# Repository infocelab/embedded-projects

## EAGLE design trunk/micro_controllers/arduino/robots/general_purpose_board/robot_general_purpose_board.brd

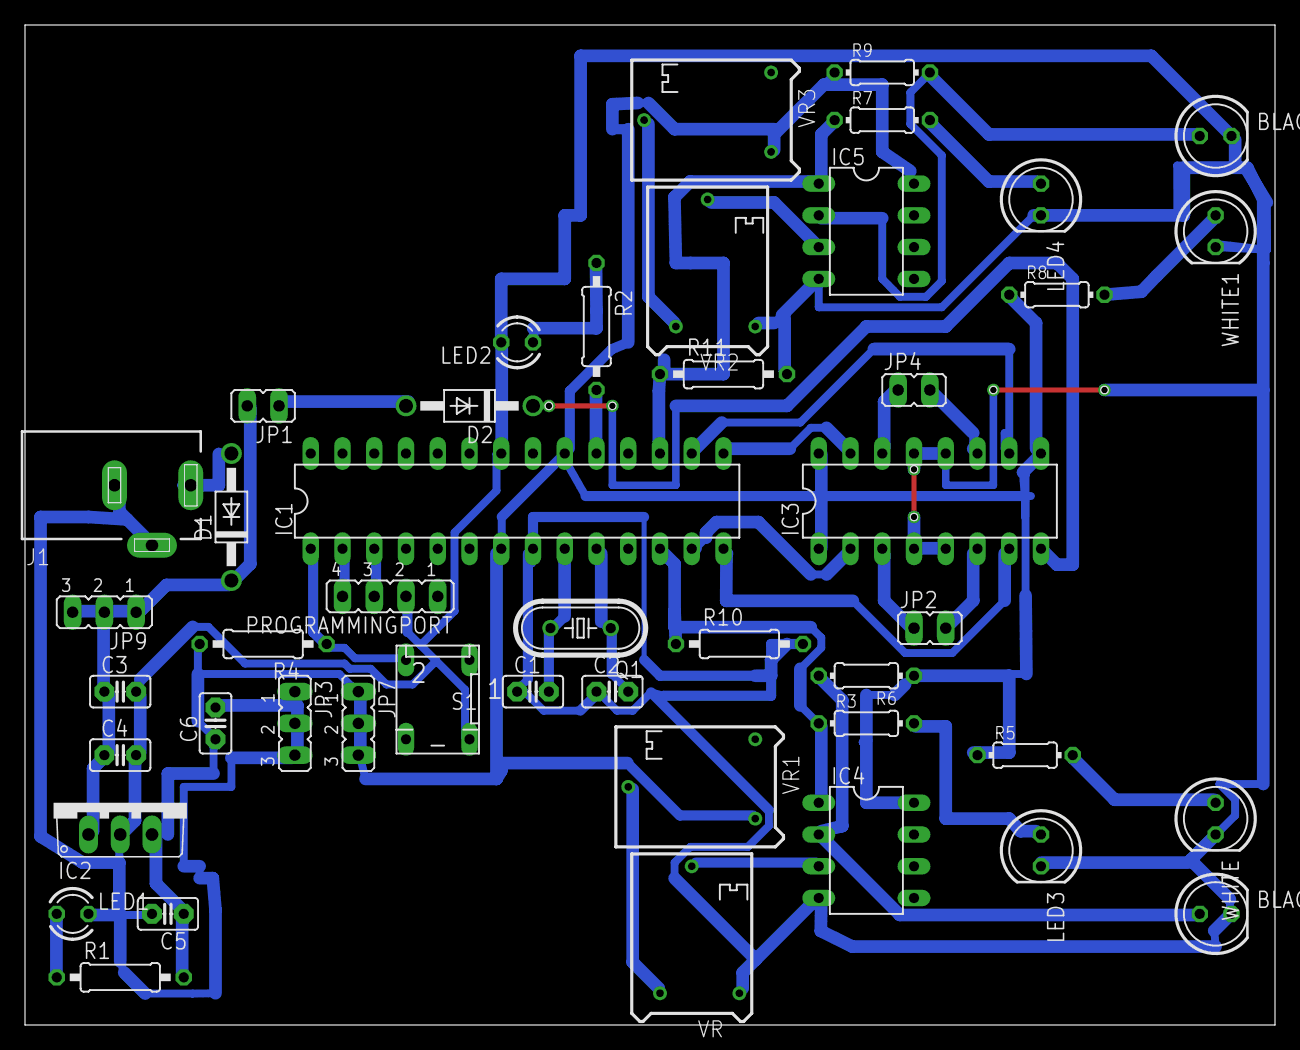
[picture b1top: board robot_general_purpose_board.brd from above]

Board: 2 copper layers, 100.0 x 80.0 mm, 46 parts (0 on the bottom side), 34 nets.

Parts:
BLACK, BLACK1: 5mm; LED5MM
C1, C2: 22pf; C2.5-2
C3: 470Uf; C2.5-2
C4, C5: 0.1uf; C2.5-2
C6: 4.7uf; C2.5-2
D1, D2: 1N4007; DO41-10
IC1: ATMEGA328; DIL28-3
IC2: 7805; TO220V
IC3: L293D; DIL16
IC4, IC5: 358; DIL-08
J1: DCJ0303
JP1, JP2, JP4: JP1
JP3: 0volt; JP2
JP7: +5v0lt; JP2
JP9: +12volt; JP2
LED1, LED2: LED3MM
LED3, LED4: 5mm; LED5MM
PROGRAMMINGPORT: JP4
Q1: 16MHZ; HC49/S
R1: 220R; 0207/10
R2: 330R; 0207/10
R3, R5, R7, R8: 1K; 0204/7
R4, R10, R11: 10K; 0207/10
R6, R9: 10K; 0204/7
S1: DP-02
VR, VR2: 50k; RTRIM64P
VR1, VR3: 100E; RTRIM64P
WHITE, WHITE1: 5mm; LED5MM

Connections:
+5V: C5.1, C6.1, IC1.7, IC1.20, IC2.3, IC3.1, IC3.9, IC3.16, IC4.8, IC5.8, JP7.1, JP7.2, JP7.3, R1.2, R4.2, R5.1, R6.1, R8.1, R9.1, VR1.3, VR3.3
+12V: C3.1, C4.1, D1.C, IC2.1, JP1.2, JP9.1, JP9.2, JP9.3
GND: BLACK.K, BLACK1.K, C1.1, C2.1, C3.2, C4.2, C5.2, C6.2, IC1.8, IC1.22, IC2.2, IC3.4, IC3.5, IC3.12, IC3.13, IC4.4, IC5.4, J1.2, J1.3, JP3.1, JP3.2, JP3.3, LED1.K, LED2.K, LED3.K, LED4.K, PROGRAMMINGPORT.2, R10.2, R11.2, S1.4, VR.1, VR2.1, WHITE.K, WHITE1.K
unnamed: C1.2, IC1.9, Q1.2
unnamed: C2.2, IC1.10, Q1.1
unnamed: D1.A, J1.1
unnamed: LED2.A, R2.1
unnamed: LED1.A, R1.1
unnamed: D2.C, IC3.8
unnamed: D2.A, JP1.1
unnamed: IC3.14, JP4.1
unnamed: IC3.11, JP4.2
unnamed: IC3.3, JP2.1
unnamed: IC3.6, JP2.2
unnamed: IC1.2, PROGRAMMINGPORT.4
unnamed: IC1.12, IC4.1, R3.1, R10.1
unnamed: R5.2, WHITE.A
unnamed: BLACK.A, IC4.2, R6.2
unnamed: IC1.15, IC3.15
unnamed: IC1.16, IC3.10
unnamed: IC1.14, IC3.7
unnamed: IC1.17, IC5.1, R7.1, R11.1
unnamed: IC1.19, R2.2
unnamed: IC4.3, VR.2
unnamed: VR.3, VR1.2
unnamed: IC1.3, PROGRAMMINGPORT.3
unnamed: IC1.1, R4.1, S1.2
unnamed: LED3.A, R3.2
unnamed: IC1.13, IC3.2
unnamed: R8.2, WHITE1.A
unnamed: BLACK1.A, IC5.2, R9.2
unnamed: IC5.3, VR2.2
unnamed: VR2.3, VR3.2
unnamed: LED4.A, R7.2

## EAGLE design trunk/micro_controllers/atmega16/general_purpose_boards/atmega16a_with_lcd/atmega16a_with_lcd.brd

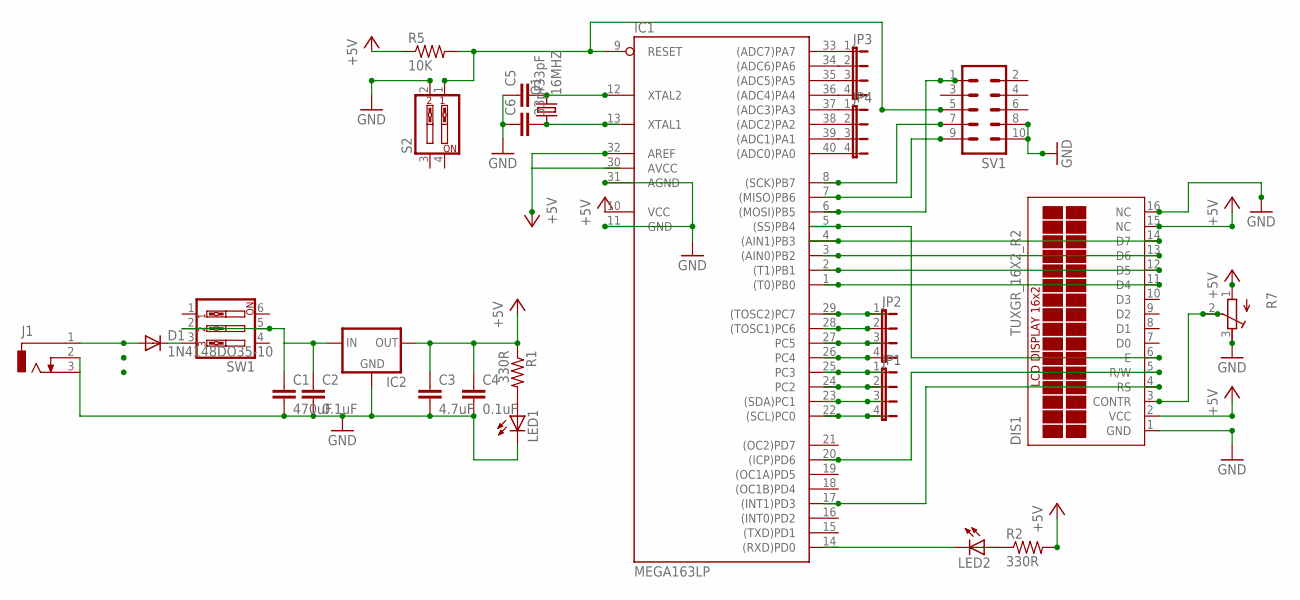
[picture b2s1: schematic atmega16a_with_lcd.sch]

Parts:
C1: 470uF; C2.5-4
C2, C4: 0.1uF; C2.5-4
C3: 4.7uF; C2.5-4
C5, C6: 33pF; C2.5-4
D1: 1N4148DO35-10; DO35-10
DIS1: TUXGR_16X2_R2
IC1: MEGA163LP; DIL40
IC2: 78XXS
J1: DCJ0303
JP1, JP2, JP3, JP4: JP4E; JP4
LED1, LED2: LED_ELD260; LED_LD260
Q1: 16MHZ; HC49U-V
R1, R2: 330R; 0204/7
R5: 10K; 0204/7
R7: R-TRIMM3339P; RTRIM3339P
S2: SW_DIP-2; EDG-02
SV1: MA05-2
SW1: SW_DIP-3; EDG-03

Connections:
+5V: C3.1, C4.1, DIS1.2 (VCC), DIS1.15 (NC), IC1.10 (VCC), IC1.32 (AREF), IC2.OUT, R1.1, R2.2, R5.1, R7.1 (E)
AVCC: IC1.30 (AVCC)
GND: C1.2, C2.2, C3.2, C4.2, C5.1, C6.1, DIS1.1 (GND), DIS1.16 (NC), IC1.11 (GND), IC1.31 (AGND), IC2.GND, J1.2, J1.3, LED1.K (C), R7.3 (A), S2.2, SV1.8, SV1.10
unnamed: D1.A, J1.1
unnamed: IC1.29 ((TOSC2)PC7), JP2.1
unnamed: C5.2, IC1.12 (XTAL2), Q1.2
unnamed: C6.2, IC1.13 (XTAL1), Q1.1
unnamed: LED1.A, R1.2
unnamed: IC1.9 (RESET), R5.2, S2.1, SV1.5
unnamed: DIS1.3 (CONTR), R7.2 (S)
unnamed: D1.C, SW1.3
unnamed: C1.1, C2.1, IC2.IN, SW1.2, SW1.5
unnamed: DIS1.11 (D4), IC1.1 ((T0)PB0)
unnamed: DIS1.12 (D5), IC1.2 ((T1)PB1)
unnamed: DIS1.13 (D6), IC1.3 ((AIN0)PB2)
unnamed: DIS1.14 (D7), IC1.4 ((AIN1)PB3)
unnamed: DIS1.4 (RS), IC1.17 ((INT1)PD3)
unnamed: DIS1.5 (R/W), IC1.20 ((ICP)PD6)
unnamed: DIS1.6 (E), IC1.5 ((SS)PB4)
unnamed: IC1.28 ((TOSC1)PC6), JP2.2
unnamed: IC1.27 (PC5), JP2.3
unnamed: IC1.26 (PC4), JP2.4
unnamed: IC1.25 (PC3), JP1.1
unnamed: IC1.24 (PC2), JP1.2
unnamed: IC1.23 ((SDA)PC1), JP1.3
unnamed: IC1.22 ((SCL)PC0), JP1.4
unnamed: IC1.6 ((MOSI)PB5), SV1.1
unnamed: IC1.7 ((MISO)PB6), SV1.9
unnamed: IC1.8 ((SCK)PB7), SV1.7
unnamed: IC1.14 ((RXD)PD0), LED2.K (C)
unnamed: IC1.33 ((ADC7)PA7), JP3.1
unnamed: IC1.34 ((ADC6)PA6), JP3.2
unnamed: IC1.35 ((ADC5)PA5), JP3.3
unnamed: IC1.36 ((ADC4)PA4), JP3.4
unnamed: IC1.37 ((ADC3)PA3), JP4.1
unnamed: IC1.38 ((ADC2)PA2), JP4.2
unnamed: IC1.39 ((ADC1)PA1), JP4.3
unnamed: IC1.40 ((ADC0)PA0), JP4.4
unnamed: LED2.A, R2.1

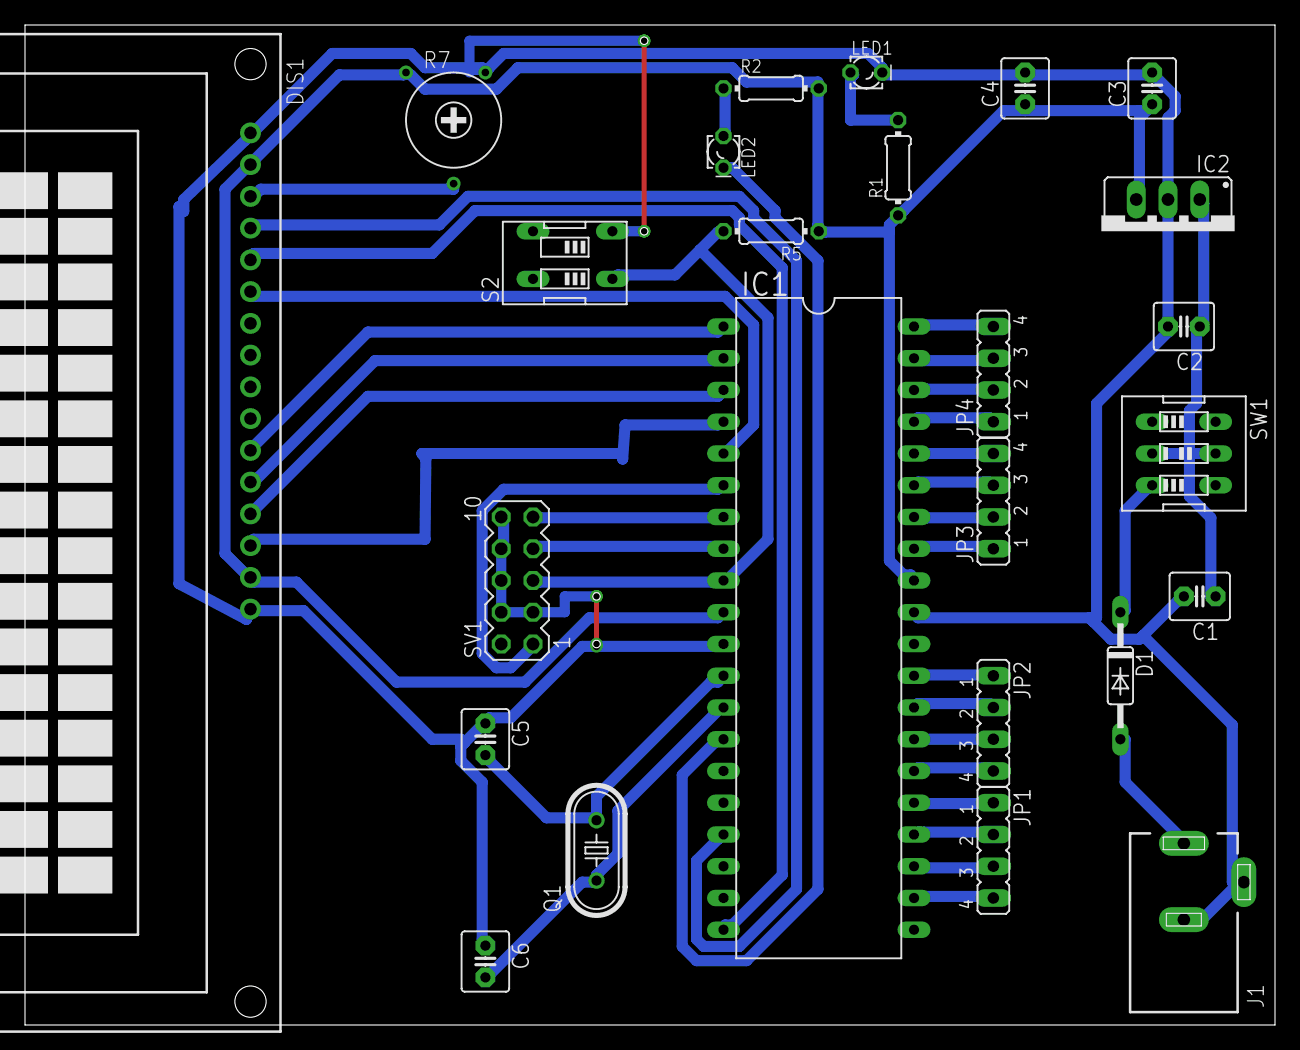
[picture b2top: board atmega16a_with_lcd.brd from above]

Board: 2 copper layers, 100.0 x 80.0 mm, 25 parts (0 on the bottom side), 38 nets.

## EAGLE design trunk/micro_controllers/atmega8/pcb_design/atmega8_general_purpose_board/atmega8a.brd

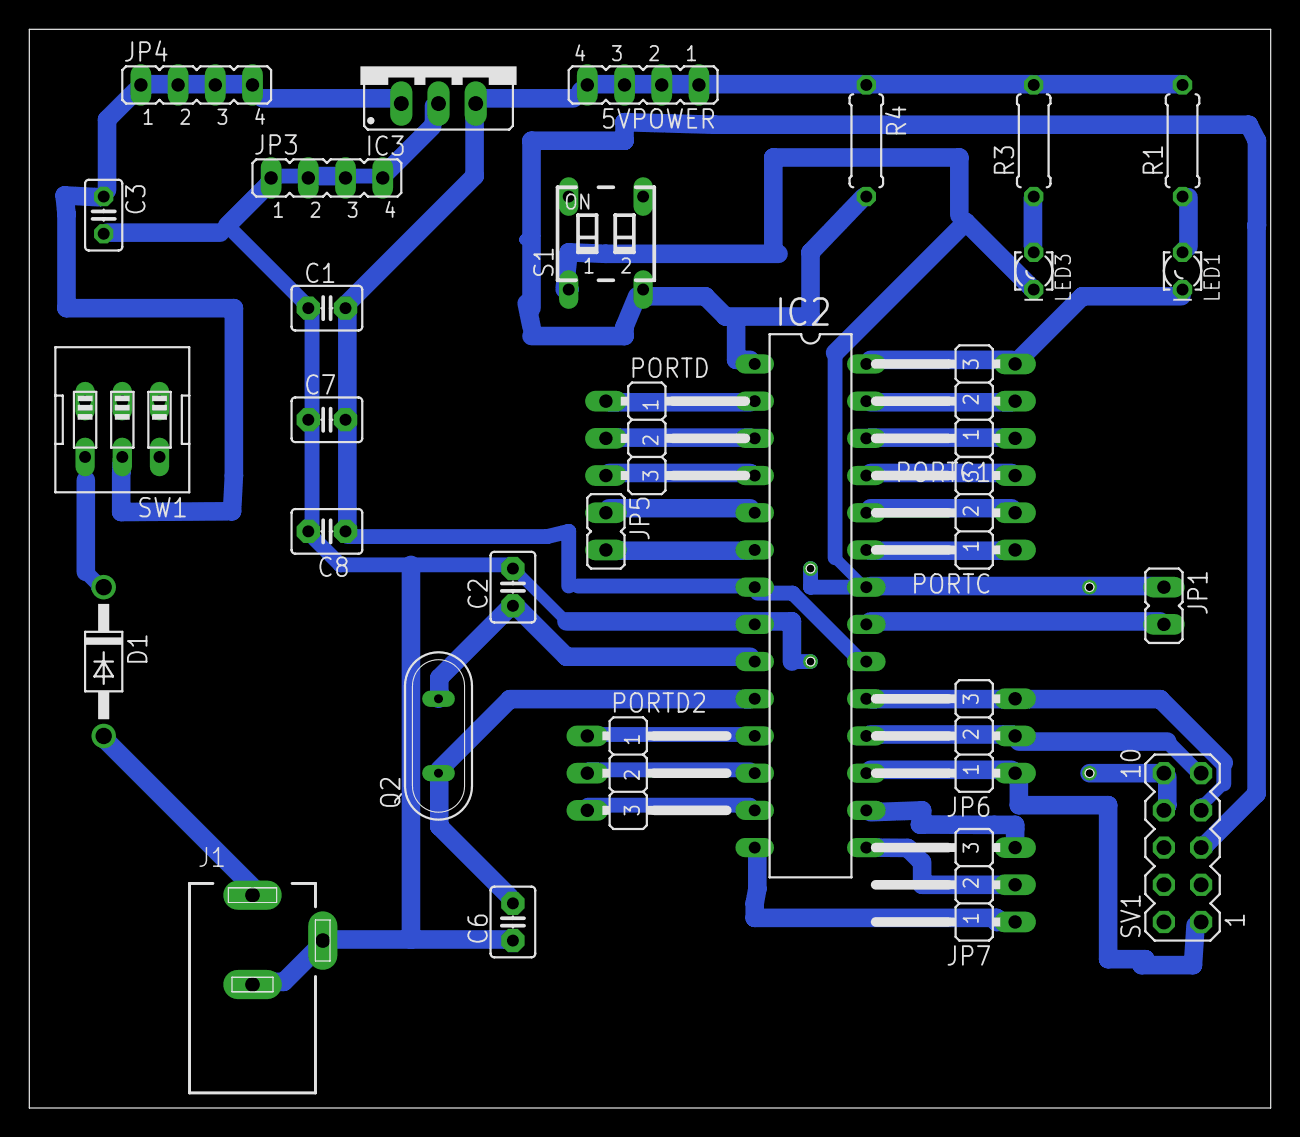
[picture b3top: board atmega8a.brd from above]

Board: 2 copper layers, 84.8 x 73.7 mm, 30 parts (0 on the bottom side), 31 nets.

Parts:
5VPOWER: 5V; JP4
C1, C7, C8: 0.1uf; C2.5-3
C2, C6: 22pf; C2.5-3
C3: 100uf; C025-025X050
D1: 1N4004; DO41-10
IC2: MEGA8-P; DIL28-3
IC3: 78XXS
J1: DCJ0202
JP1, JP5: JP1
JP3: GND; JP4
JP4: 12V; JP4
JP6, JP7: JP2W
LED1, LED3: LED_LD260
PORTC, PORTC1: JP2W
PORTD, PORTD2: JP2W
Q2: QS
R1, R3: 330R; 0207/7
R4: 10K; 0207/7
S1: SD4-02
SV1: MA05-2
SW1: EDG-03

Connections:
unnamed: C3.1, IC3.IN, JP4.1, JP4.2, JP4.3, JP4.4, SW1.5
unnamed: LED1.A, R1.1
unnamed: D1.A, J1.1
unnamed: IC2.23, PORTC.1
unnamed: IC2.24, PORTC.2
unnamed: IC2.25, PORTC.3
unnamed: IC2.26, PORTC1.1
unnamed: D1.C, SW1.4
unnamed: LED3.A, R3.1
unnamed: C2.1, IC2.9, Q2.2
unnamed: C6.2, IC2.10, Q2.1
unnamed: 5VPOWER.1, 5VPOWER.2, 5VPOWER.3, 5VPOWER.4, C1.2, C7.2, C8.1, IC2.7, IC2.20, IC3.OUT, R1.2, R3.2, R4.1
unnamed: IC2.27, PORTC1.2
unnamed: IC2.28, LED1.K, PORTC1.3
unnamed: IC2.2, PORTD.1
unnamed: IC2.3, PORTD.2
unnamed: IC2.4, PORTD.3
unnamed: IC2.5, JP5.1
unnamed: IC2.6, JP5.2
unnamed: IC2.14, JP7.1
unnamed: IC2.15, JP7.2
unnamed: IC2.16, JP7.3
unnamed: IC2.17, JP6.1, SV1.1
unnamed: IC2.18, JP6.2, SV1.9
unnamed: IC2.19, JP6.3, SV1.7
unnamed: C1.1, C2.2, C3.2, C6.1, C7.1, C8.2, IC2.22, IC3.GND, J1.2, J1.3, JP1.1, JP3.1, JP3.2, JP3.3, JP3.4, LED3.K, S1.4, SV1.8, SV1.10
unnamed: IC2.1, R4.2, S1.3, SV1.5
unnamed: IC2.11, PORTD2.1
unnamed: IC2.12, PORTD2.2
unnamed: IC2.13, PORTD2.3
unnamed: IC2.21, JP1.2

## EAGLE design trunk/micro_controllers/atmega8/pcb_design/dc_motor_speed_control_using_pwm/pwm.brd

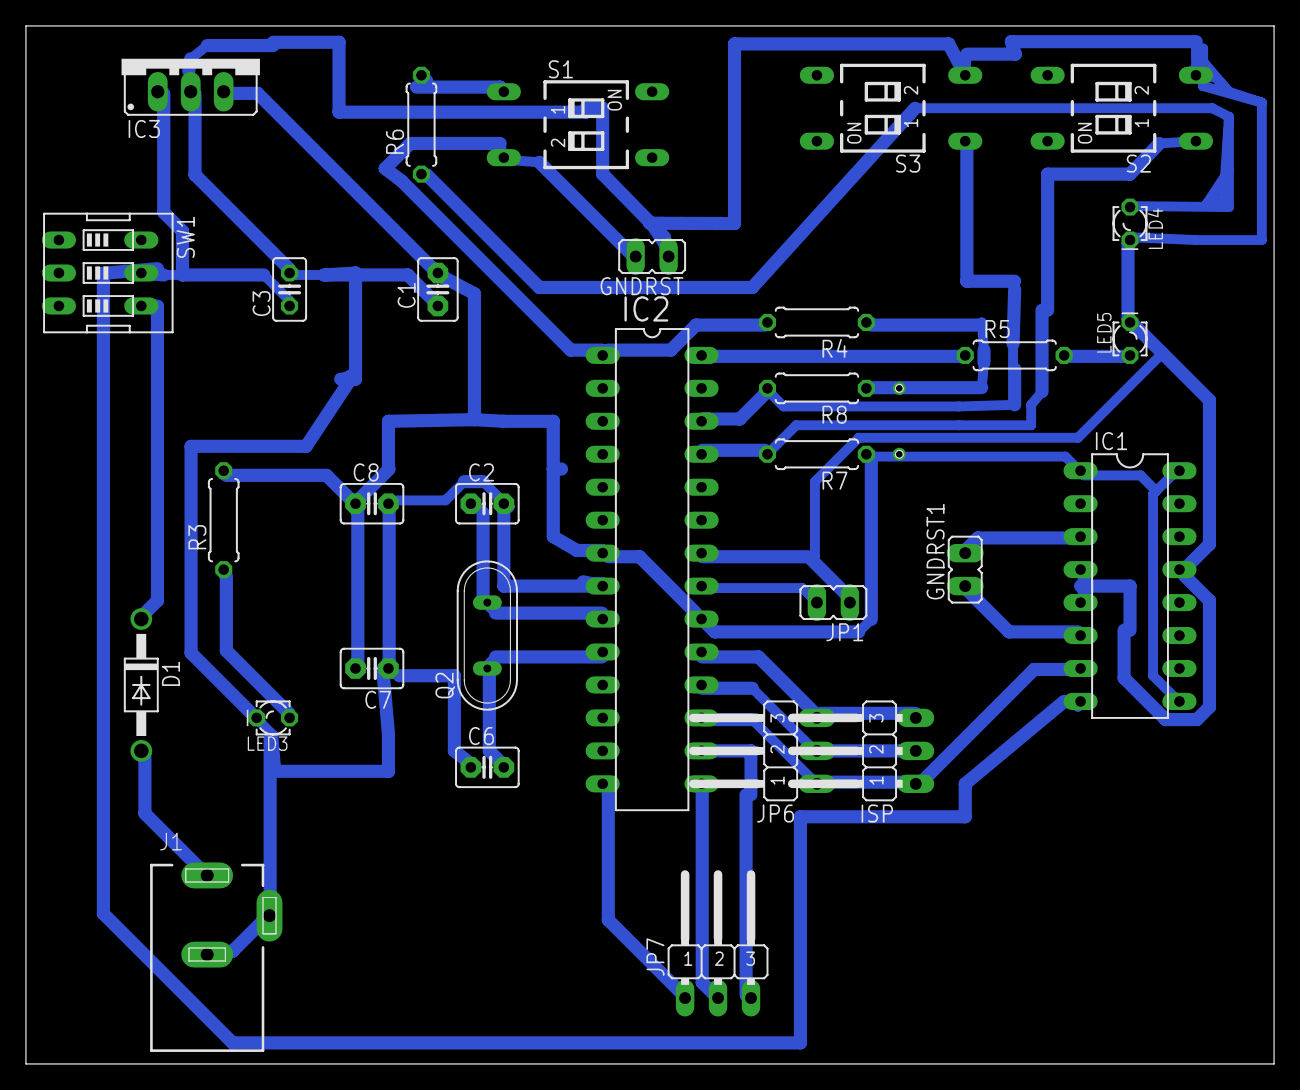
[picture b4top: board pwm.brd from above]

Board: 2 copper layers, 96.2 x 80.0 mm, 31 parts (0 on the bottom side), 24 nets.

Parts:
C1, C7, C8: 0.1uf; C2.5-3
C2, C6: 22pf; C2.5-3
C3: 100uf; C025-025X050
D1: 1N4004; DO41-10
GNDRST, GNDRST1: JP1
IC1: L293D; DIL16
IC2: MEGA8-P; DIL28-3
IC3: 78XXS
ISP: JP2W
J1: DCJ0202
JP1: JP1
JP6, JP7: JP2W
LED3, LED4, LED5: LED_LD260
Q2: QS
R3, R6: 330R; 0207/7
R4, R7, R8: 10K; 0207/7
R5: 0207/7
S1, S2, S3: SD4-02
SW1: EDG-03

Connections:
unnamed: C3.1, IC1.8, IC3.IN, SW1.5
unnamed: D1.A, J1.1
unnamed: GNDRST1.2, IC1.3
unnamed: GNDRST1.1, IC1.6
unnamed: C1.1, C2.2, C3.2, C6.1, C7.1, C8.2, GNDRST.1, IC1.4, IC1.5, IC1.13, IC2.8, IC2.22, IC3.GND, J1.2, J1.3, JP1.1, LED3.K, LED4.K, LED5.K, S2.2, S3.2
unnamed: D1.C, SW1.4
unnamed: LED3.A, R3.1
unnamed: C2.1, IC2.9, Q2.2
unnamed: C6.2, IC2.10, Q2.1
unnamed: C1.2, C7.2, C8.1, IC1.1, IC1.9, IC1.16, IC2.7, IC2.20, IC3.OUT, R3.2, R4.1, R7.1, R8.1
unnamed: LED4.A, R6.1
unnamed: IC2.25, R7.2, S2.1
unnamed: IC2.26, R8.2, S3.1
unnamed: IC2.28, R5.1
unnamed: IC2.14, JP7.1
unnamed: IC2.15, JP7.2
unnamed: IC2.16, JP7.3
unnamed: IC1.7, IC2.17, ISP.1, JP6.1
unnamed: IC2.18, ISP.2, JP6.2
unnamed: IC2.19, ISP.3, JP6.3
unnamed: LED5.A, R5.2
unnamed: R6.2, S1.1
unnamed: GNDRST.2, IC2.1, R4.2, S1.2
unnamed: IC2.21, JP1.2

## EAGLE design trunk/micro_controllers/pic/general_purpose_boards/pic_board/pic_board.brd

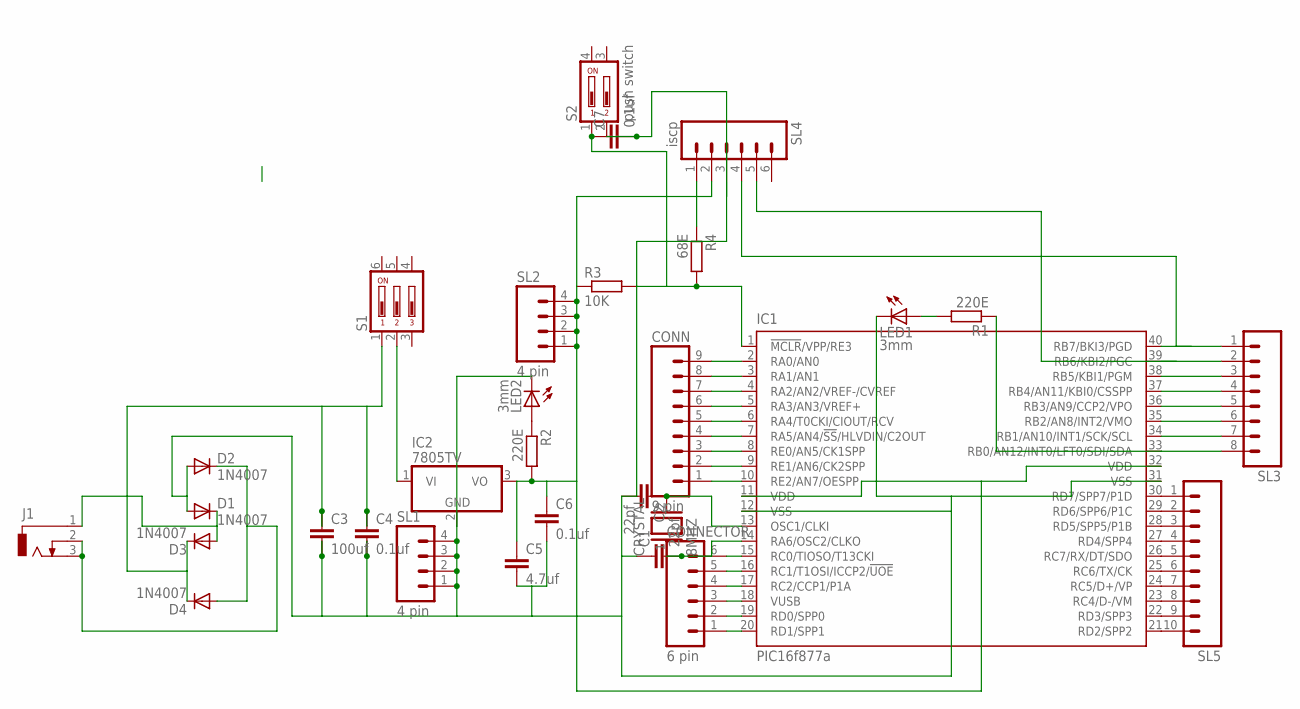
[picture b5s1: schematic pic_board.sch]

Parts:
C1, C2: 22pf; C2.5-2
C3: 100uf; C5B7.2
C4, C7: 0.1uf; C2.5-3
C5: 4.7uf; C5B7.2
C6: 0.1uf; C2.5-2
CONN: 9 pin; 09P
CONNECTOR: 6 pin; 06P
CRYSTAL: 8MHZ; QS
D1, D2, D3, D4: 1N4007; DO41-10
IC1: PIC16f877a; DIL40
IC2: 7805TV; TO220V
J1: DCJ0303
LED1, LED2: 3mm; LED3MM
R1, R2: 220E; 0204/7
R3: 10K; 0204/7
R4: 68E; 0204/7
S1: DA03; DA-03
S2: push switch; DP-02
SL1, SL2: 4 pin; 04P
SL3: M08; 08P
SL4: iscp; 06P
SL5: M10; 10P

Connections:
unnamed: C2.1, CRYSTAL.2, IC1.13 (OSC1/CLKI)
unnamed: C1.2, CRYSTAL.1, IC1.14 (RA6/OSC2/CLKO)
unnamed: LED1.A, R1.2
unnamed: CONN.1, IC1.10 (RE2/AN7/OESPP)
unnamed: CONN.2, IC1.9 (RE1/AN6/CK2SPP)
unnamed: CONN.3, IC1.8 (RE0/AN5/CK1SPP)
unnamed: CONN.4, IC1.7 (RA5/AN4/!SS!/HLVDIN/C2OUT)
unnamed: CONN.5, IC1.6 (RA4/T0CKI/CIOUT/RCV)
unnamed: CONN.6, IC1.5 (RA3/AN3/VREF+)
unnamed: CONN.7, IC1.4 (RA2/AN2/VREF-/CVREF)
unnamed: CONN.8, IC1.3 (RA1/AN1)
unnamed: CONN.9, IC1.2 (RA0/AN0)
unnamed: CONNECTOR.1, IC1.20 (RD1/SPP1)
unnamed: CONNECTOR.2, IC1.19 (RD0/SPP0)
unnamed: CONNECTOR.3, IC1.18 (VUSB)
unnamed: CONNECTOR.4, IC1.17 (RC2/CCP1/P1A)
unnamed: CONNECTOR.5, IC1.16 (RC1/T1OSI/ICCP2/!UOE)
unnamed: CONNECTOR.6, IC1.15 (RC0/TIOSO/T13CKI)
unnamed: IC1.40 (RB7/BKI3/PGD), SL3.1, SL4.4
unnamed: IC1.39 (RB6/KBI2/PGC), SL3.2, SL4.5
unnamed: IC1.38 (RB5/KBI1/PGM), SL3.3
unnamed: IC1.37 (RB4/AN11/KBI0/CSSPP), SL3.4
unnamed: IC1.36 (RB3/AN9/CCP2/VPO), SL3.5
unnamed: IC1.35 (RB2/AN8/INT2/VMO), SL3.6
unnamed: IC1.34 (RB1/AN10/INT1/SCK/SCL), SL3.7
unnamed: IC1.30 (RD7/SPP7/P1D), SL5.1
unnamed: IC1.29 (RD6/SPP6/P1C), SL5.2
unnamed: IC1.28 (RD5/SPP5/P1B), SL5.3
unnamed: IC1.33 (RB0/AN12/INT0/LFT0/SDI/SDA), R1.1, SL3.8
unnamed: C3.1, C4.1, D3.C, D4.C, S1.1
unnamed: D2.C, D4.A, J1.2, J1.3
unnamed: D1.C, D3.A, J1.1
unnamed: C5.1, C6.1, IC1.11 (VDD), IC1.32 (VDD), IC2.3 (VO), R2.2, R3.1, SL2.1, SL2.2, SL2.3, SL2.4, SL4.2
unnamed: LED2.A, R2.1
unnamed: C1.1, C2.2, C3.2, C4.2, C5.2, C6.2, C7.2, D1.A, D2.A, IC1.12 (VSS), IC1.31 (VSS), IC2.2 (GND), LED1.K (C), LED2.K (C), S2.2, SL1.1, SL1.2, SL1.3, SL1.4, SL4.3
unnamed: IC1.27 (RD4/SPP4), SL5.4
unnamed: IC1.26 (RC7/RX/DT/SDO), SL5.5
unnamed: IC1.25 (RC6/TX/CK), SL5.6
unnamed: C7.1, IC1.1 (!MCLR!/VPP/RE3), R3.2, R4.2, S2.1
unnamed: IC1.24 (RC5/D+/VP), SL5.7
unnamed: IC1.23 (RC4/D-/VM), SL5.8
unnamed: IC1.22 (RD3/SPP3), SL5.9
unnamed: IC1.21 (RD2/SPP2), SL5.10
unnamed: R4.1, SL4.1
unnamed: IC2.1 (VI), S1.2

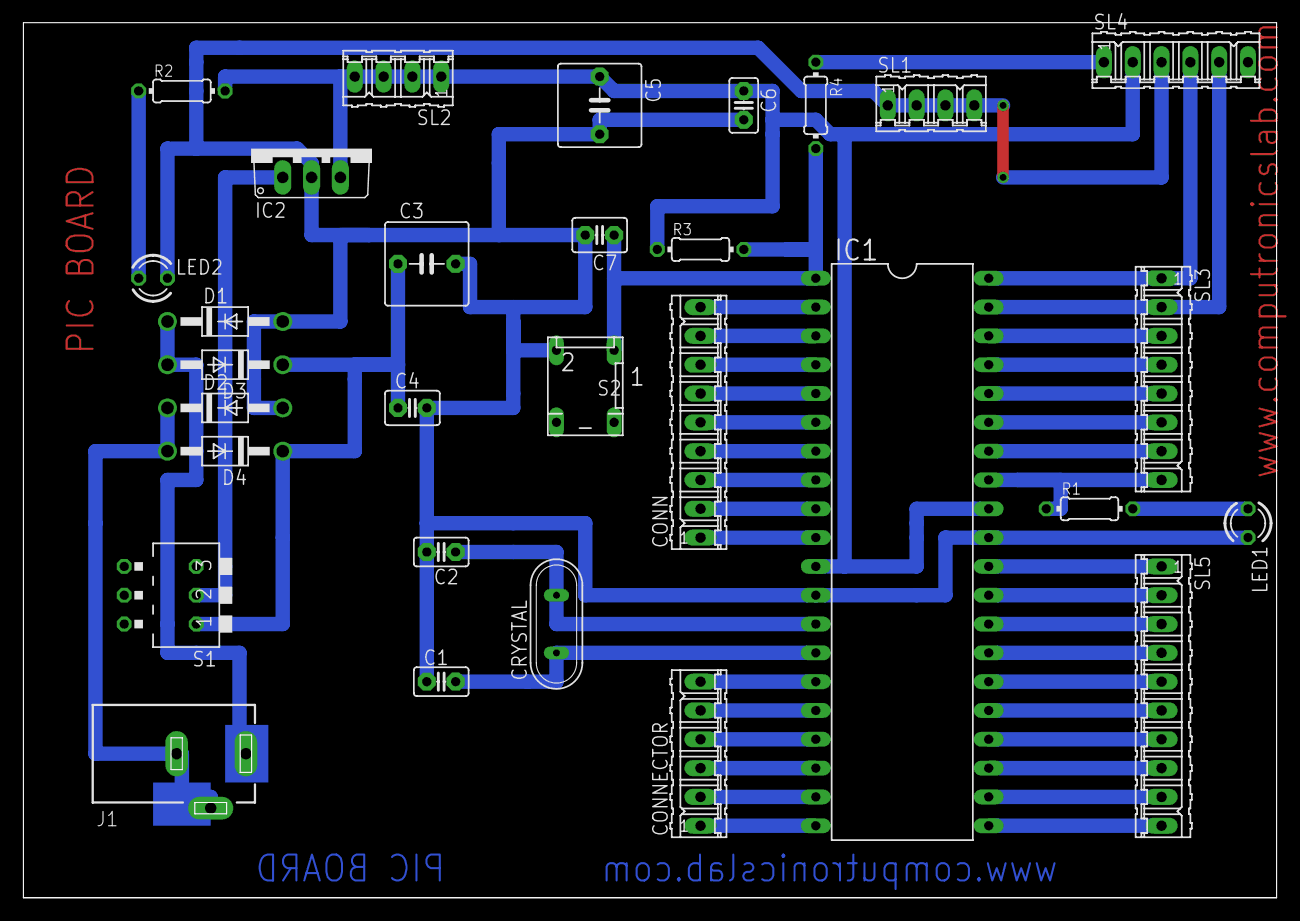
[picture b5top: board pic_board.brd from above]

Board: 2 copper layers, 110.5 x 77.1 mm, 30 parts (0 on the bottom side), 45 nets.

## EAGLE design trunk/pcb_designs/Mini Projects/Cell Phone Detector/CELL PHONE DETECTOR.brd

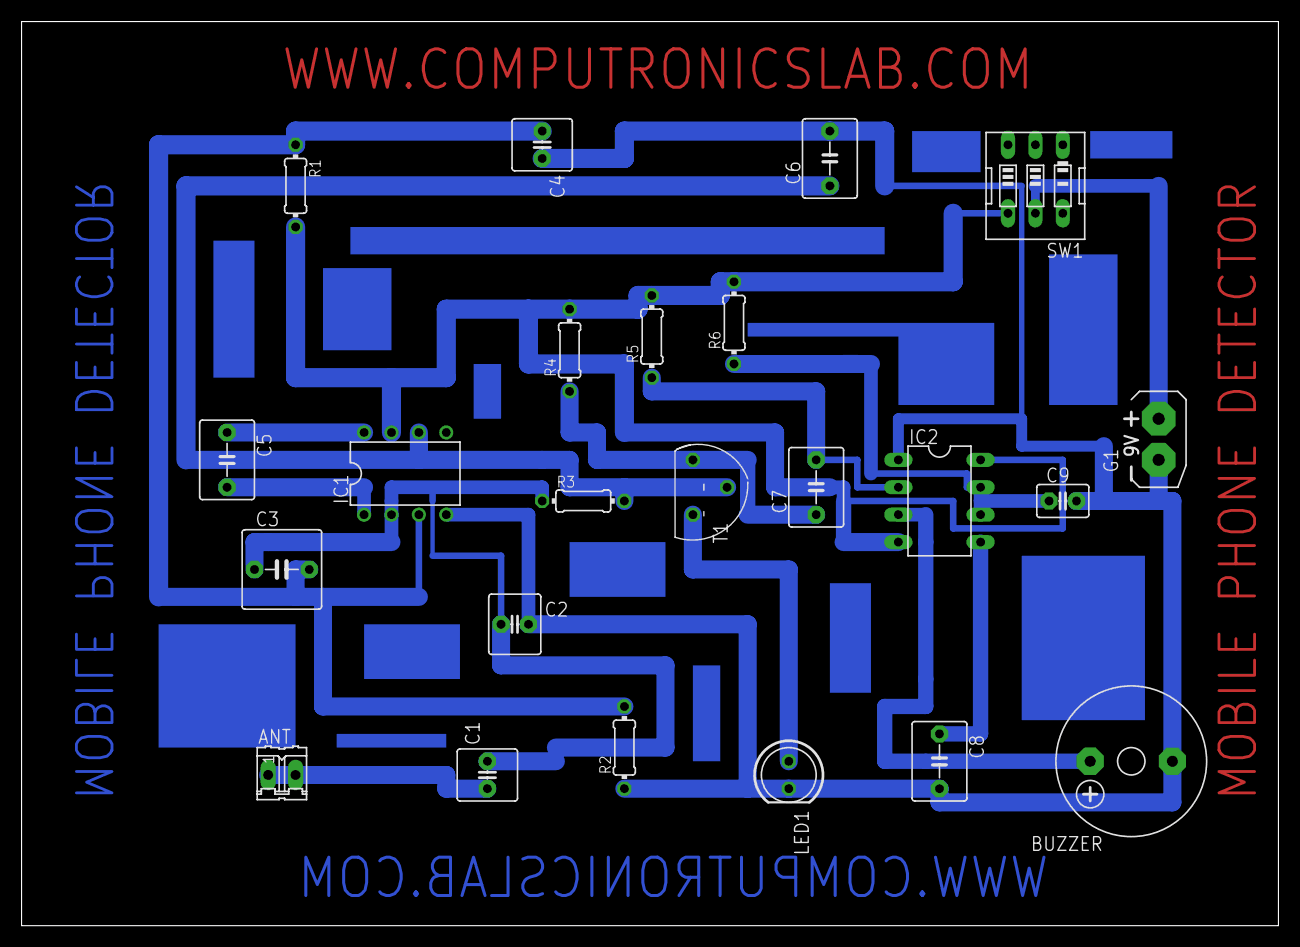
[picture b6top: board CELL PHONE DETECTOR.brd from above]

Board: 2 copper layers, 116.5 x 83.8 mm, 23 parts (0 on the bottom side), 15 nets.

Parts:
ANT: 02P
BUZZER: F/CM12P
C1, C2: 22PF; C2.5-6
C3: .22uf; C5B7.2
C4: 100uf; C2.5-6
C5: 47PF; C5B5
C6: 0.1uf(104); C5B5
C7: 0.1uf; C5B5
C8: 0.01uf(103); C5B5
C9: 4.7uf; C2.5-3
G1: AB9V
IC1: CA3130; DIL08
IC2: NE555; DIL-08
LED1: 5MM; LED5MM
R1, R3: 2.2ME; 0204/7
R2: 100K; 0204/7
R4: 1K; 0204/7
R5: 12K; 0204/7
R6: 15K; 0204/7
SW1: ON/OFF SWITCH; EDG-03
T1: BC547; TO92

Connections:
unnamed: C3.2, C4.1, IC1.3, R1.1, R2.2
unnamed: C1.2, C2.1, C3.1, IC1.2, R3.1
unnamed: ANT.1, ANT.2, C1.1
unnamed: BUZZER.-, C2.2, C4.2, C6.2, C8.2, C9.2, G1.-, IC1.4, IC2.1, LED1.K, R2.1
unnamed: C6.1, IC1.6, R3.2, T1.2
unnamed: C5.2, IC1.1
unnamed: C5.1, IC1.8
unnamed: LED1.A, T1.1
unnamed: C7.1, R4.1, T1.3
unnamed: C7.2, IC2.2, R5.1
unnamed: IC1.7, IC2.4, IC2.8, R1.2, R4.2, R5.2, R6.2, SW1.4
unnamed: C9.1, IC2.6, IC2.7, R6.1
unnamed: C8.1, IC2.5
unnamed: BUZZER.+, IC2.3
unnamed: G1.+, SW1.5

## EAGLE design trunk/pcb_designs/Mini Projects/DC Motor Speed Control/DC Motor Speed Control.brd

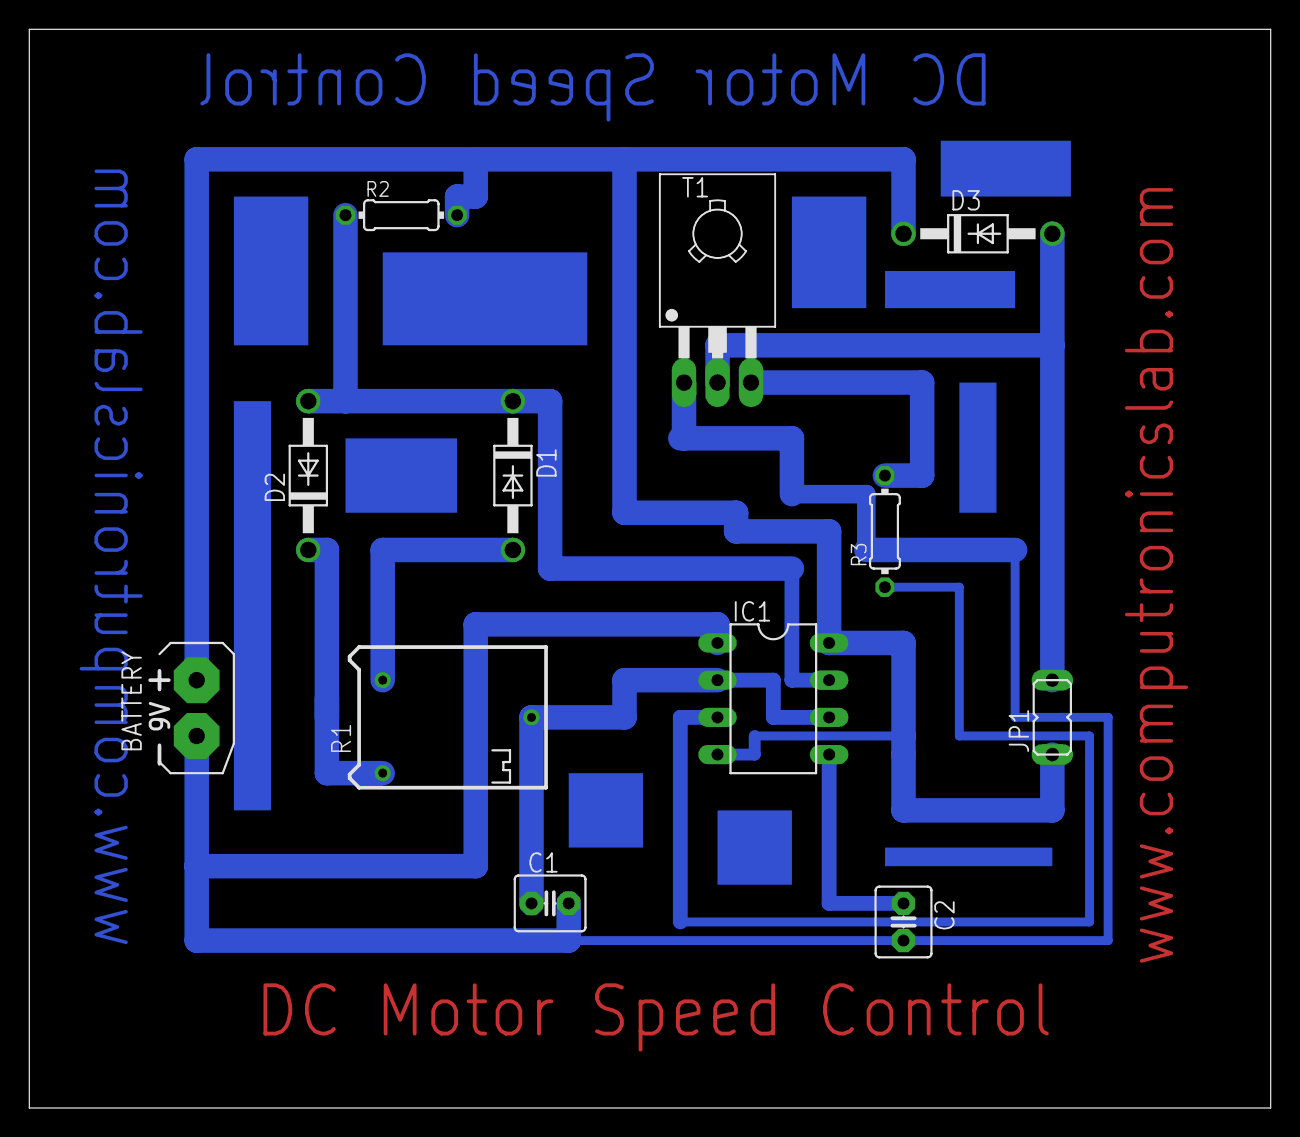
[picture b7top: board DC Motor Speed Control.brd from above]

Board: 2 copper layers, 84.8 x 73.7 mm, 12 parts (0 on the bottom side), 10 nets.

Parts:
BATTERY: 9V; AB9V
C1: 0.1uf; C2.5-4
C2: 0.01uf; C2.5-4
D1, D2, D3: 1N4007; DO41-10
IC1: NE555; DIL-08
JP1: motor; JP1
R1: 50k; RTRIM64P
R2: 1K; 0204/7
R3: 33E; 0204/7
T1: BD139; TO126

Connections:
unnamed: R3.2, T1.3
unnamed: C1.1, IC1.2, IC1.6, R1.2
unnamed: D1.C, D2.A, IC1.7, R2.1
unnamed: BATTERY.+, D3.C, IC1.4, IC1.8, JP1.1, R2.2
unnamed: D2.C, R1.1
unnamed: D1.A, R1.3
unnamed: C2.1, IC1.5
unnamed: BATTERY.-, C1.2, C2.2, IC1.1, T1.1
unnamed: IC1.3, R3.1
unnamed: D3.A, JP1.2, T1.2
